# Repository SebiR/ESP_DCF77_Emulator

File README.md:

# ESProgrammer
A simple ESP8266 (ESP-01) module to emulate a DCF77 receiver using NTP time

## Features
* Open Collector output
* Selectable pullup (5V or 3.3V)

# Firmware
The firmware is not from me. It is based on an old Elektor project and has been modified by Fuso68. I found it somewhere on the interwebs. I might create my own in the future

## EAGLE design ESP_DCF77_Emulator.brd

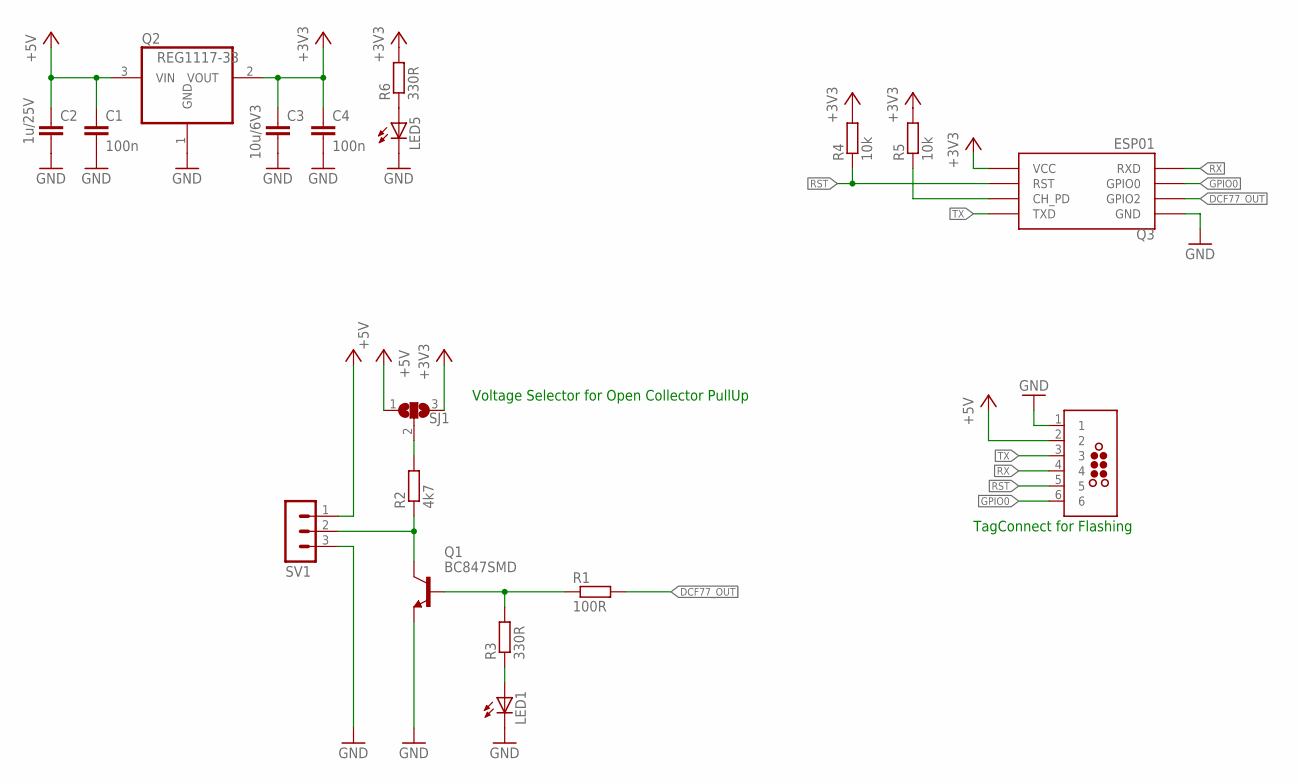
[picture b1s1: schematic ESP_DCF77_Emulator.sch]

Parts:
C1, C4: 100n; C0603
C2: 1u/25V; C0603
C3: 10u/6V3; C0603
J6: TC2030-MCP-NL
LED1, LED5: LEDCHIP-LED0603; CHIP-LED0603
Q1: BC847SMD; SOT23
Q2: REG1117-33; SOT223
Q3: ESP01
R1: 100R; R0603
R2: 4k7; R0603
R3, R6: 330R; R0603
R4, R5: 10k; R0603
SJ1: SJ2W; SJ_2
SV1: MA03-1

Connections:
+3V3: C3.1, C4.1, Q2.2 (VOUT), Q3.VCC, R4.2, R5.2, R6.2, SJ1.3
+5V: C1.1, C2.1, J6.2, Q2.3 (VIN), SJ1.1, SV1.1
DCF77_OUT: Q3.GPIO2, R1.2
GND: C1.2, C2.2, C3.2, C4.2, J6.1, LED1.C, LED5.C, Q1.2 (E), Q2.1 (GND), Q3.GND, SV1.3
GPIO0: J6.6, Q3.GPIO0
unnamed: Q1.3 (C), R2.1, SV1.2
unnamed: Q1.1 (B), R1.1, R3.2
unnamed: R2.2, SJ1.2
unnamed: LED1.A, R3.1
unnamed: Q3.CH_PD, R5.1
unnamed: LED5.A, R6.1
RST: J6.5, Q3.RST, R4.1
RX: J6.4, Q3.RX (RXD)
TX: J6.3, Q3.TX (TXD)

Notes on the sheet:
TagConnect for Flashing
Voltage Selector for Open Collector PullUp

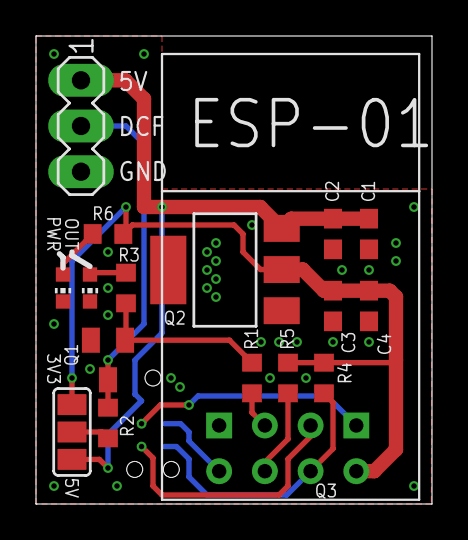
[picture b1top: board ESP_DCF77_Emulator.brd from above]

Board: 2 copper layers, 22.0 x 26.0 mm, 18 parts (1 on the bottom side), 14 nets.

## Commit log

2023-08-05 added .gitignore to versioned files Firmware is now in another folder to make the Arduino IDE happy

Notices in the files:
parts and their libraries:
tag-connect: ©2009 ROFA.cz - modified and updated by Robert Darlington ‹rdarlington@gmail.com›
